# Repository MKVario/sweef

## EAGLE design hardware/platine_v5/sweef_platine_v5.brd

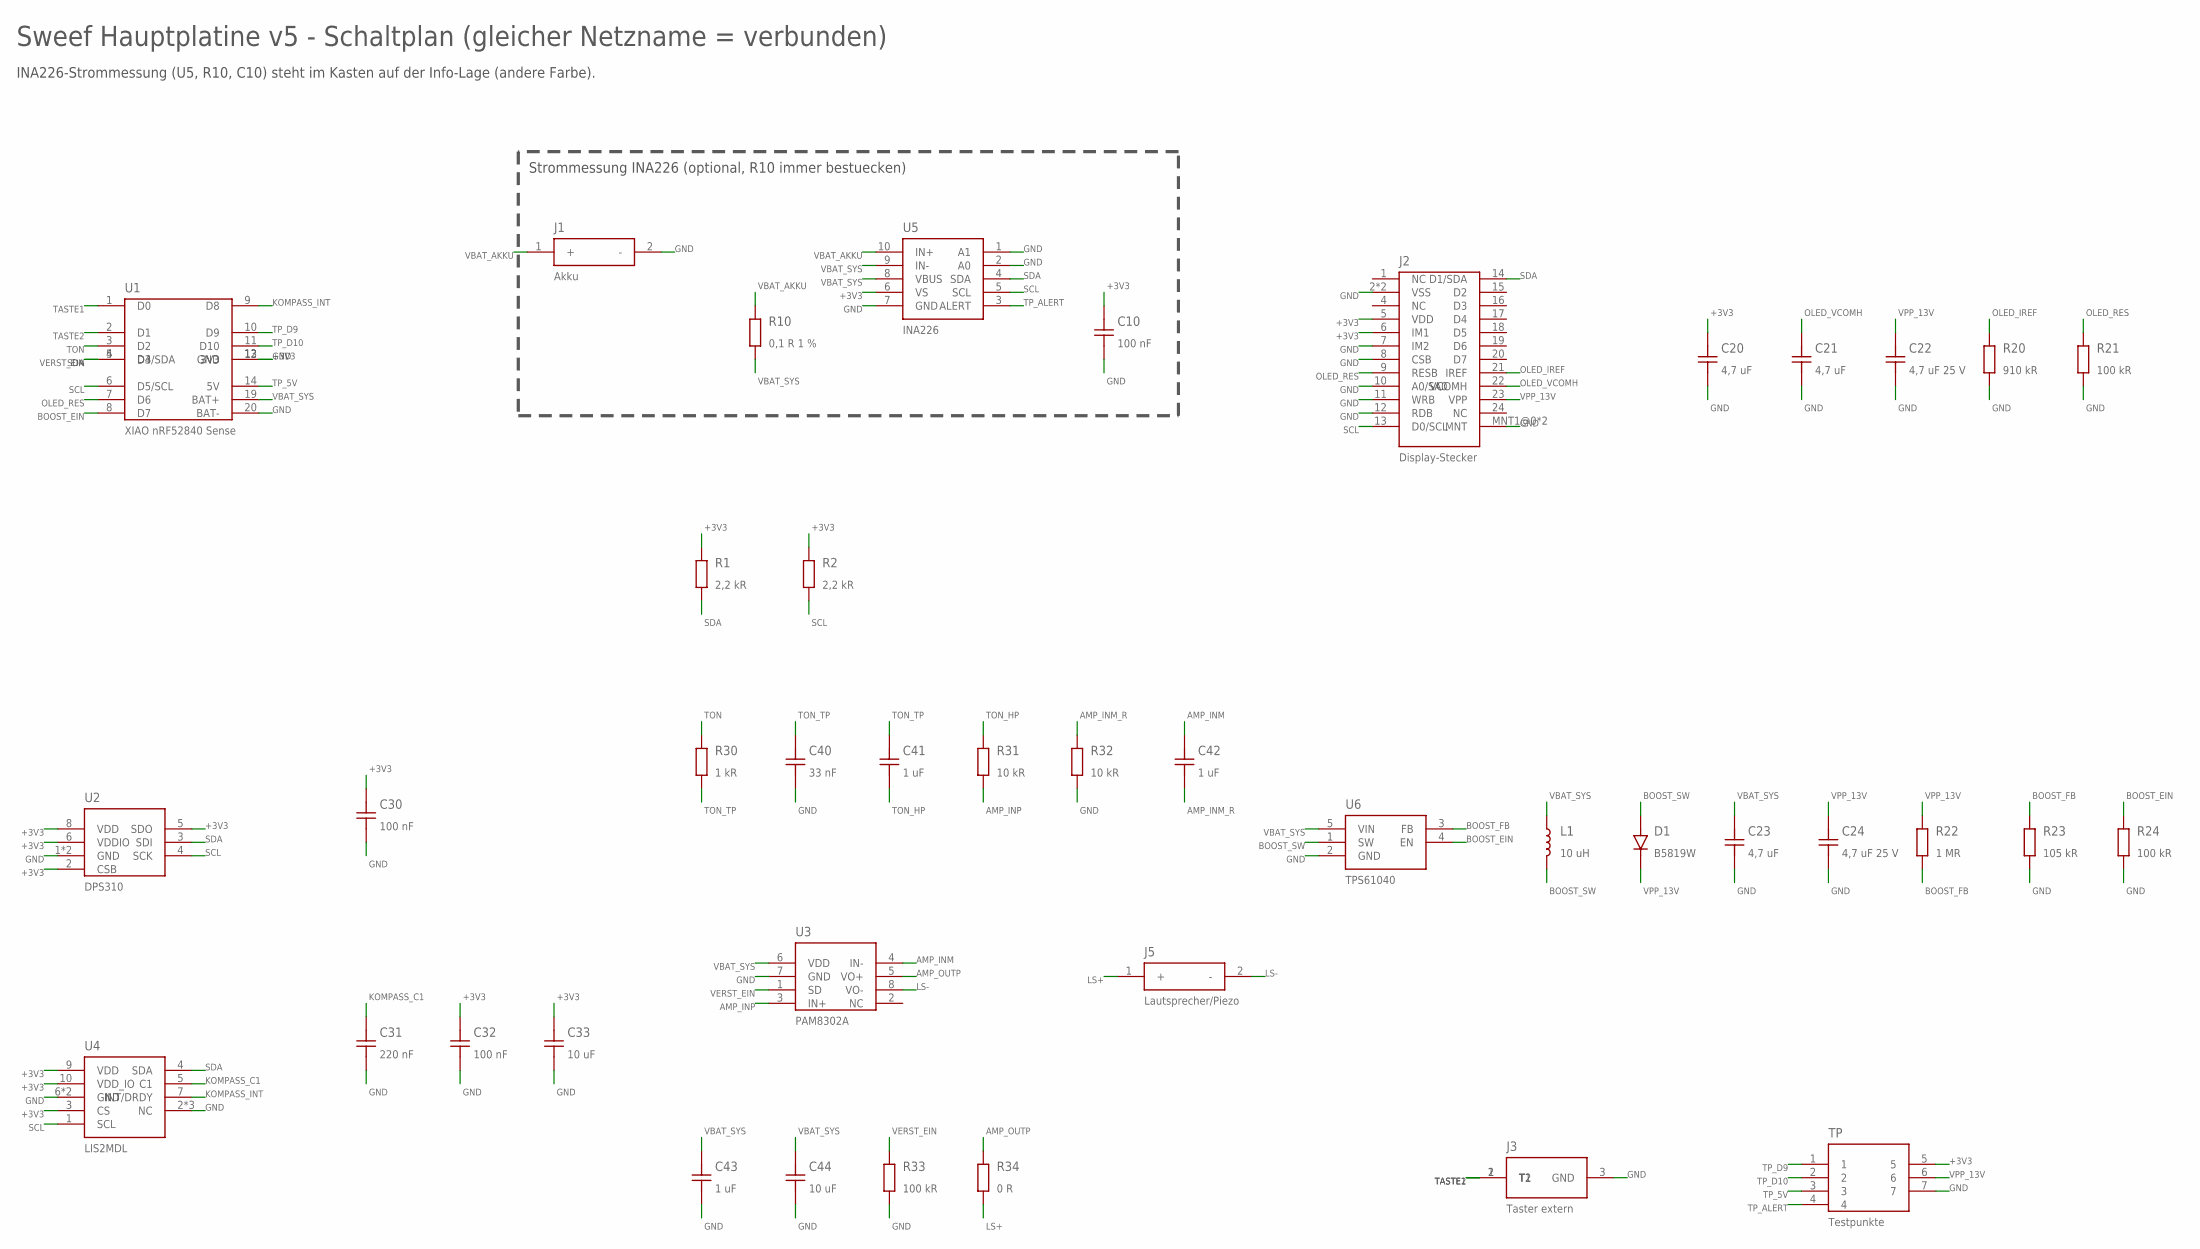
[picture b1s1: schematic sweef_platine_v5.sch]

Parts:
C10, C30, C32: 100 nF; C0402
C20, C21, C23: 4,7 uF; 0603-NO
C22, C24: 4,7 uF 25 V; 0805-NO
C31: 220 nF; C0402
C33, C44: 10 uF; 0603-NO
C40: 33 nF; C0402
C41, C42, C43: 1 uF; C0402
D1: B5819W; SOD-123
J1: Akku; PADS_2_AKKU
J2: Display-Stecker; FPC-24_XUNPU_FPC-05FB-24PH20
J3: Taster extern; PADS_3_TASTER
J5: Lautsprecher/Piezo; PADS_2_LS
L1: 10 uH; INDUCTOR_3X3
R1, R2: 2,2 kR; R0402
R10: 0,1 R 1 %; 0805-NO
R20: 910 kR; R0402
R21, R24, R33: 100 kR; R0402
R22: 1 MR; R0402
R23: 105 kR; R0402
R30: 1 kR; R0402
R31, R32: 10 kR; R0402
R34: 0 R; 0603-NO
TP: Testpunkte; TP_7
U1: XIAO nRF52840 Sense; XIAO_NRF52840_SMD
U2: DPS310; BMX280_COMBO
U3: PAM8302A; MSOP8_0.65MM
U4: LIS2MDL; LGA12_2X2MM
U5: INA226; MSOP10
U6: TPS61040; SOT23-5

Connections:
+3V3: C10.1, C20.1, C30.1, C32.1, C33.1, J2.5 (VDD), J2.6 (IM1), R1.1, R2.1, TP.5, U1.12 (3V3), U2.2 (CSB), U2.5 (SDO), U2.6 (VDDIO), U2.8 (VDD), U4.3 (CS), U4.9 (VDD), U4.10 (VDD_IO), U5.6 (VS)
AMP_INM: C42.1, U3.4 (IN-)
AMP_INM_R: C42.2, R32.1
AMP_INP: R31.2, U3.3 (IN+)
AMP_OUTP: R34.1, U3.5 (VO+)
BOOST_EIN: R24.1, U1.8 (D7), U6.4 (EN)
BOOST_FB: R22.2, R23.1, U6.3 (FB)
BOOST_SW: D1.A (1), L1.P$2 (2), U6.1 (SW)
GND: C10.2, C20.2, C21.2, C22.2, C23.2, C24.2, C30.2, C31.2, C32.2, C33.2, C40.2, C43.2, C44.2, J1.2 (-), J2.2 (VSS), J2.3 (VSS), J2.7 (IM2), J2.8 (CSB), J2.10 (A0/SA0), J2.11 (WRB), J2.12 (RDB), J2.MNT1@0 (MNT), J2.MNT2@0 (MNT), J3.3 (GND), R20.2, R21.2, R23.2, R24.2, R32.2, R33.2, TP.7, U1.13 (GND), U1.20 (BAT-), U2.1 (GND), U2.7 (GND), U3.7 (GND), U4.2 (NC), U4.6 (GND), U4.8 (GND), U4.11 (NC), U4.12 (NC), U5.1 (A1), U5.2 (A0), U5.7 (GND), U6.2 (GND)
KOMPASS_C1: C31.1, U4.5 (C1)
KOMPASS_INT: U1.9 (D8), U4.7 (INT/DRDY)
LS+: J5.1 (+), R34.2
LS-: J5.2 (-), U3.8 (VO-)
OLED_IREF: J2.21 (IREF), R20.1
OLED_RES: J2.9 (RESB), R21.1, U1.7 (D6)
OLED_VCOMH: C21.1, J2.22 (VCOMH)
SCL: J2.13 (D0/SCL), R2.2, U1.6 (D5/SCL), U2.4 (SCK), U4.1 (SCL), U5.5 (SCL)
SDA: J2.14 (D1/SDA), R1.2, U1.5 (D4/SDA), U2.3 (SDI), U4.4 (SDA), U5.4 (SDA)
TASTE1: J3.1 (T1), U1.1 (D0)
TASTE2: J3.2 (T2), U1.2 (D1)
TON: R30.1, U1.3 (D2)
TON_HP: C41.2, R31.1
TON_TP: C40.1, C41.1, R30.2
TP_5V: TP.3, U1.14 (5V)
TP_ALERT: TP.4, U5.3 (ALERT)
TP_D9: TP.1, U1.10 (D9)
TP_D10: TP.2, U1.11 (D10)
VBAT_AKKU: J1.1 (+), R10.1, U5.10 (IN+)
VBAT_SYS: C23.1, C43.1, C44.1, L1.P$1 (1), R10.2, U1.19 (BAT+), U3.6 (VDD), U5.8 (VBUS), U5.9 (IN-), U6.5 (VIN)
VERST_EIN: R33.1, U1.4 (D3), U3.1 (SD)
VPP_13V: C22.1, C24.1, D1.C (2), J2.23 (VPP), R22.1, TP.6

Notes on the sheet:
Sweef Hauptplatine v5 - Schaltplan (gleicher Netzname = verbunden)
INA226-Strommessung (U5, R10, C10) steht im Kasten auf der Info-Lage (andere Farbe).
Strommessung INA226 (optional, R10 immer bestuecken)

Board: 2 copper layers, 41 parts (36 on the bottom side), 31 nets, no tracks yet.

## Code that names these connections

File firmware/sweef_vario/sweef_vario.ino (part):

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int   TON_SINK     = 600;   // Hz Sinkalarm
int   TAKT_LANGSAM = 750;   // ms Piep+Pause bei schwachem Steigen
int   TAKT_SCHNELL = 280;   // ms Piep+Pause beim Steigen von TON_SKALA
int   PIEP_ANTEIL  = 50;    // Prozent des Takts, in dem der Ton klingt
float TON_SKALA    = 18.75; // m/s, hier ist der Ton am hoechsten/schnellsten

// Ton am Boden: erst nach erkanntem Start piepen (Ground-Handling)
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// Nullschieber: leises Ticken, wenn es kaum noch sinkt (Thermik/Hang-Kante)
bool  NULLSCHIEBER   = false;
float NULL_AB        = -0.3;   // m/s, ab hier tickt es (bis zum Steigton)
const int NULL_FREQ  = 380;    // Hz, tiefer Ton
// Display um 180 Grad drehen (Vario andersherum am Gurt)
bool  DISPLAY_DREHEN = false;
int   HELLIGKEIT     = 100;  // Display-Helligkeit in % (per Handy einstellbar)
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const float OHNE_IMU_REAKTION = 2.0;

// ---------- Anschluesse ----------
const int PIN_TON    = D2;
const int PIN_VERST  = D3;
const int PIN_TASTE1 = D0;
const int PIN_TASTE2 = D1;

Adafruit_DPS310 dps;
#if DISPLAY_KLEIN
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// Dort haengt das nackte Displayglas: 13-V-Wandler an D7 (BOOST_EIN, mit
// Pulldown) und Display-Reset an D6 (OLED_RES, mit Pulldown). Ohne die
// beiden Leitungen bleibt das Display dunkel.
const int PIN_OLED_RES  = D6;
const int PIN_BOOST_EIN = D7;
bool platine = false;

bool platineErkennen() {
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// dann VPP aus.
void anzeigeStrom(bool an) {
  if (an) {
    if (platine) { digitalWrite(PIN_BOOST_EIN, HIGH); delay(5); }
    anzeige.setPowerSave(0);
  } else {
    anzeige.setPowerSave(1);
    if (platine) digitalWrite(PIN_BOOST_EIN, LOW);
  }
}

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bool frageAktiv() { return frageBis && (long)(millis() - frageBis) < 0; }
void frageBox();

bool taste1() { return digitalRead(PIN_TASTE1) == LOW; }
bool taste2() { return digitalRead(PIN_TASTE2) == LOW; }

bool usbSteckt() {
  uint8_t sdAn = 0;
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  uint32_t top = 16000000UL / (uint32_t)freq;
  if (top > 32767) top = 32767;
  HwPWM3.setMaxValue(top);
  HwPWM3.writePin(PIN_TON, top * LAUT_TABELLE[stufe] / 1000);
}

void tonEin(int freq) {
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  anzeigeStrom(false);                         // Display aus
  if (platine) {
    inaSchlafen();                                 // Strommessung aus
    digitalWrite(PIN_OLED_RES, LOW);               // Display im Reset, kein Strom ueber R21
  }
  if (sensorOk) dps.setMode(DPS310_IDLE);          // Drucksensor schlafen
  digitalWrite(PIN_LSM6DS3TR_C_POWER, LOW);        // Bewegungssensor aus
  warteTaste1Los();                                // sonst sofort wieder wach
  systemOff(PIN_TASTE1, LOW);
}

void selbsttest();
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void setup() {
  pinMode(PIN_VERST, OUTPUT);
  digitalWrite(PIN_VERST, LOW);
  pinMode(PIN_TASTE1, INPUT_PULLUP);
  pinMode(PIN_TASTE2, INPUT_PULLUP);
  HwPWM3.setClockDiv(PWM_PRESCALER_PRESCALER_DIV_1);   // 16 MHz
  HwPWM3.addPin(PIN_TON);

  Serial.begin(115200);
  Wire.begin();
  platine = platineErkennen();
  if (platine) {                     // Platine v5: 13 V an, Display-Reset (>10 us), loslassen
    pinMode(PIN_BOOST_EIN, OUTPUT);
    pinMode(PIN_OLED_RES, OUTPUT);
    digitalWrite(PIN_OLED_RES, LOW);
    digitalWrite(PIN_BOOST_EIN, HIGH);
    delay(10);
    digitalWrite(PIN_OLED_RES, HIGH);
    delay(5);
  }
  anzeige.setI2CAddress(0x3C * 2);   // neues Display: Adresse fest auf 0x3C
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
